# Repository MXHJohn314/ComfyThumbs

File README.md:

# ComfyThumbs

A column-staggered keyboard inspired by comfortable and efficient thumb use and keycap compatibility.

### The Default Keymap
<h5><b>Comfy Thumbs (v3)</b></h5>

[Check out the Gist on Keyboard Layout Editor](http://www.keyboard-layout-editor.com/#/gists/36e706f383088aca6e862086f8b5e326)

<p>

### High Keycap Compatibility

Comfy Thumbs has the highest keycap compatibility of any column-staggered board. Space and Backspace are the only keys that are not traditionally-sized. That means you won't need to buy/use different keycaps for `Right Shift`, `Left Shift`, `Enter`, `Tab`, `\ `, `Command`, `Ctrl`, `Alt`, `OS`, and `Application` keys. Just chose any Standard ANSI keycap set (99% of keycap sets), and you're good to go!. 

<p>

### Use your thumbs without hurting them

|Thumb Cluster Style|# of keys|Avg. reach from Home Position|
|---|---|---|
|ComfyThumbs|6|1u
|Manuform/Dactyl-Manuform|6|3.5u
|Maltron/Dacyl/Kenesis/Ergodox|6-8|4.5u

Unlike other large thumb cluster designs that waste valuable space by pushing the cluster away from resting thumb position or building the cluster on a convex plane, all thumb keys are within 1u radius of resting position. The thumbs naturally rest on either `Space` or `Backspace`, with `Shift`, `Ctrl`, `Alt` and `OS` nearby. There are two thumb rows; `Space`, `Backspace`, and both `Shift` keys have a higher profile on the upper thumb row to distinguish thumb location by feel.

### Comfy Thumbs = Comfy Pinkies
Your pinkies have been doing way more work than they should. That's why modifiers have moved to the thumb cluster. Adding to that, the index fingers have a new inner column for `Tab`, `\ `, `-`, `=`,  `[` and `]`.

Keyboard Maintainer: [MXHJohn314](https://mxhjohn314.github.io/)  

### Compiling the Firmware

See the [build environment setup](Todo) and the [make instructions](Todo) for more information. Brand new to ZMK? Start with our [Complete Newbs Guide](Todo).

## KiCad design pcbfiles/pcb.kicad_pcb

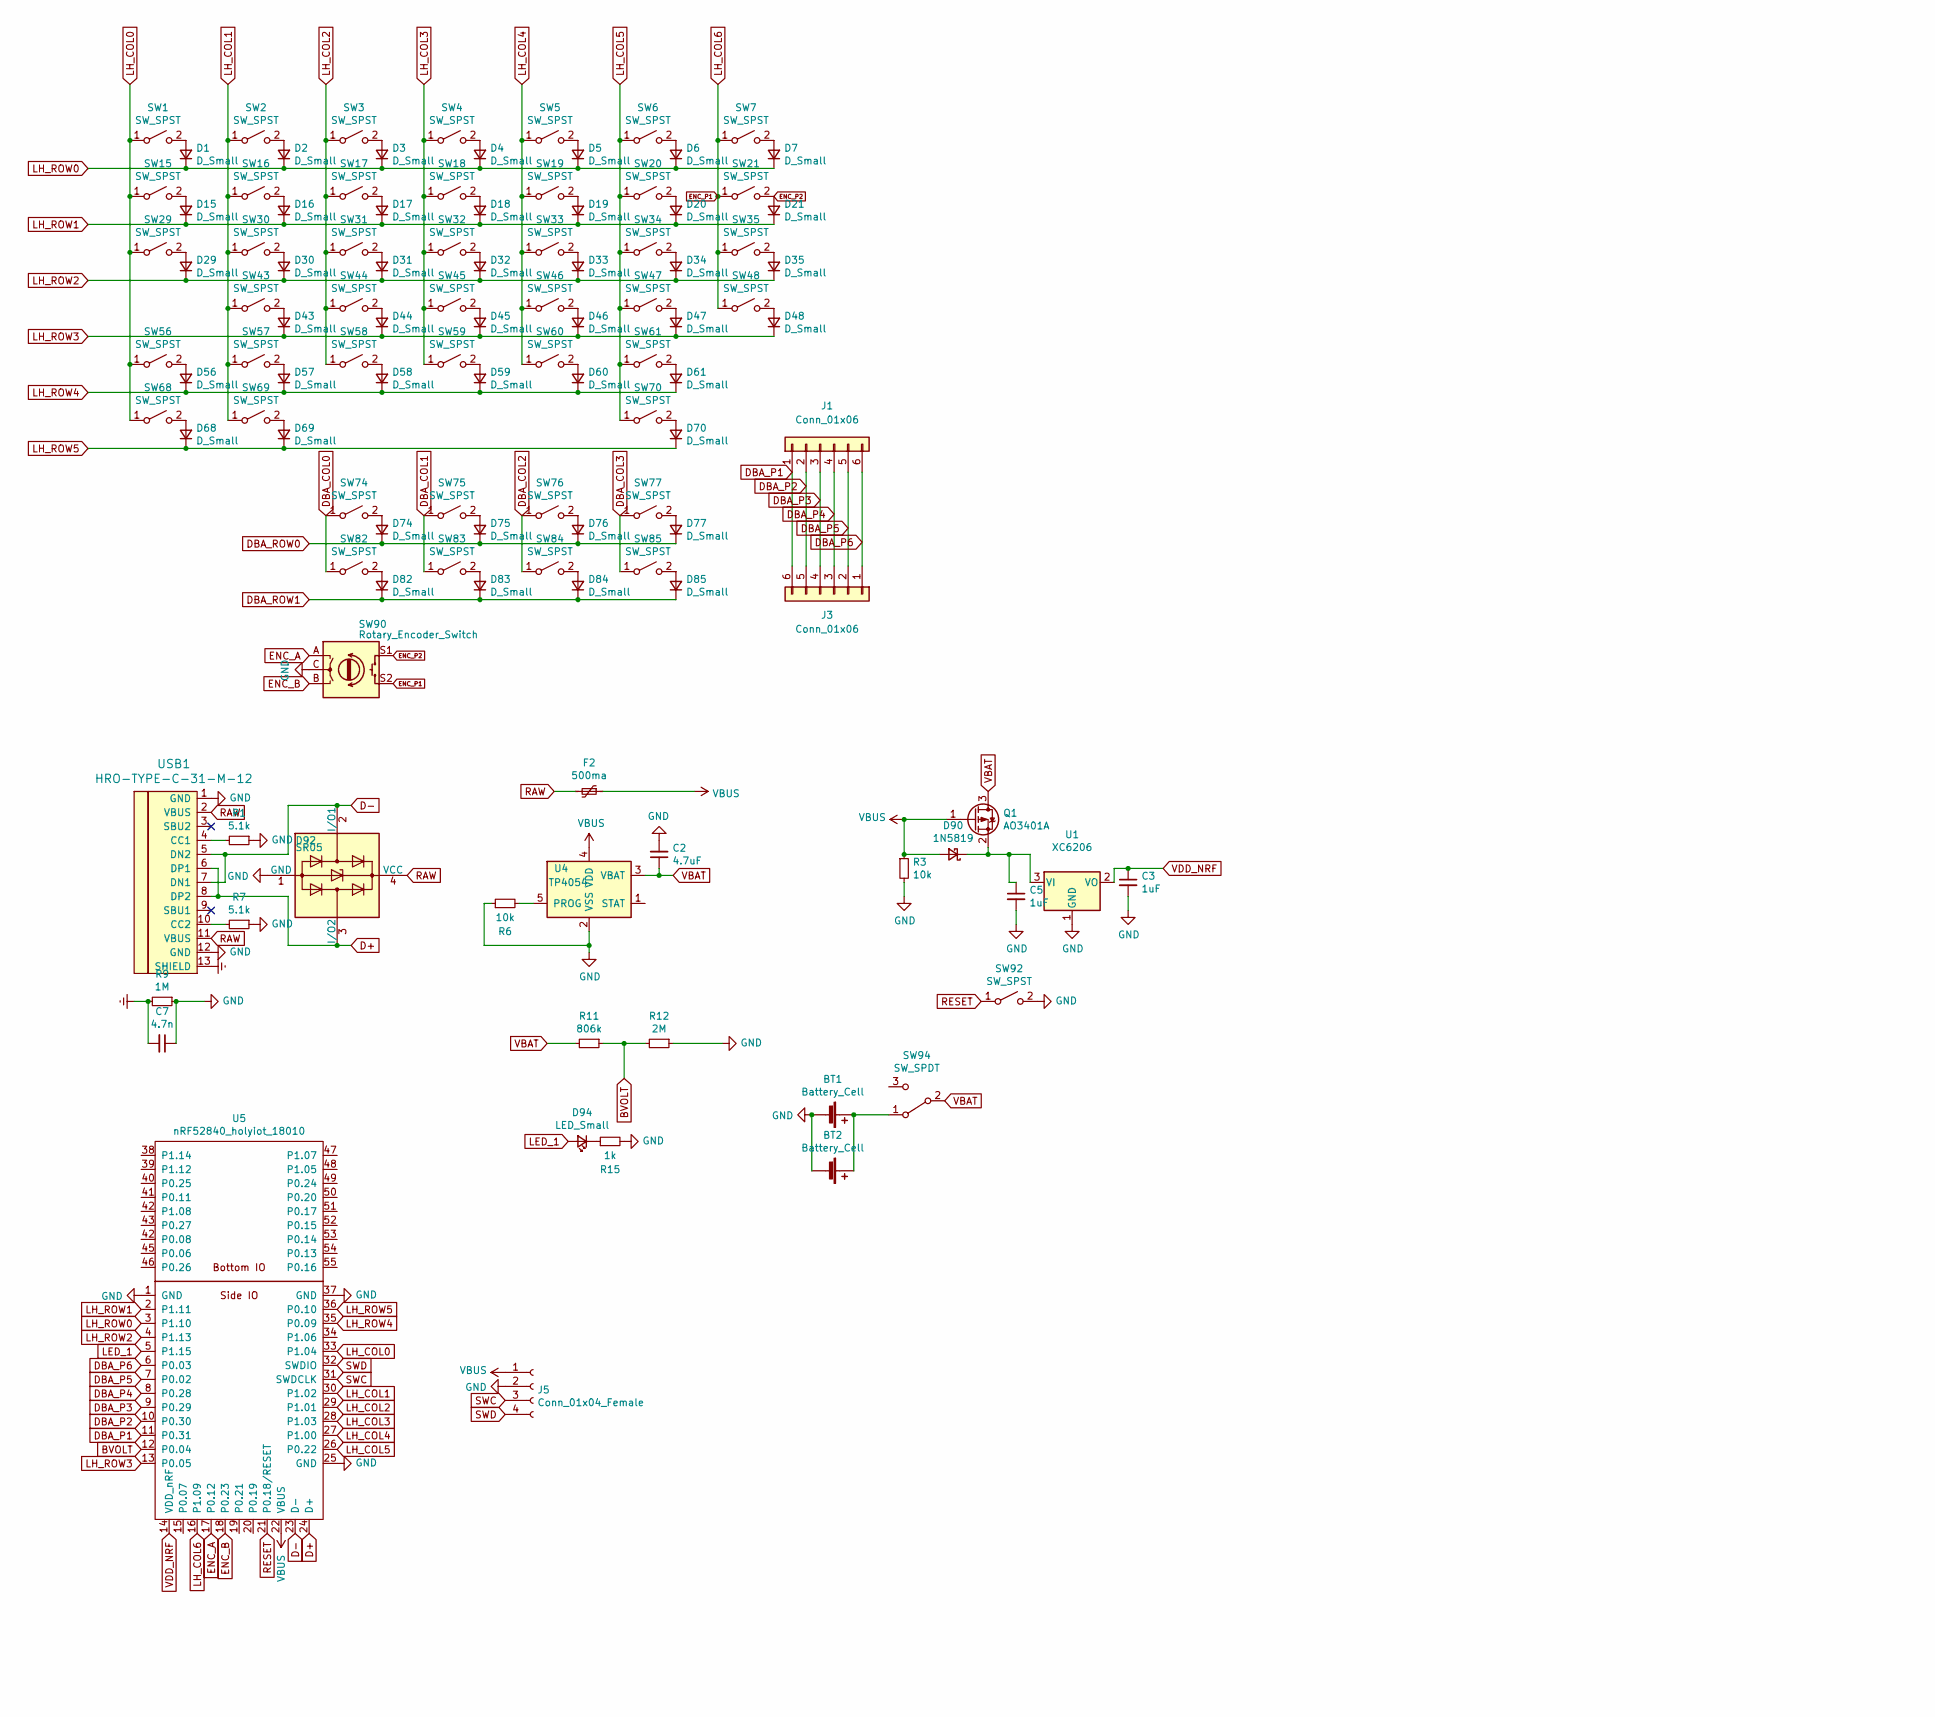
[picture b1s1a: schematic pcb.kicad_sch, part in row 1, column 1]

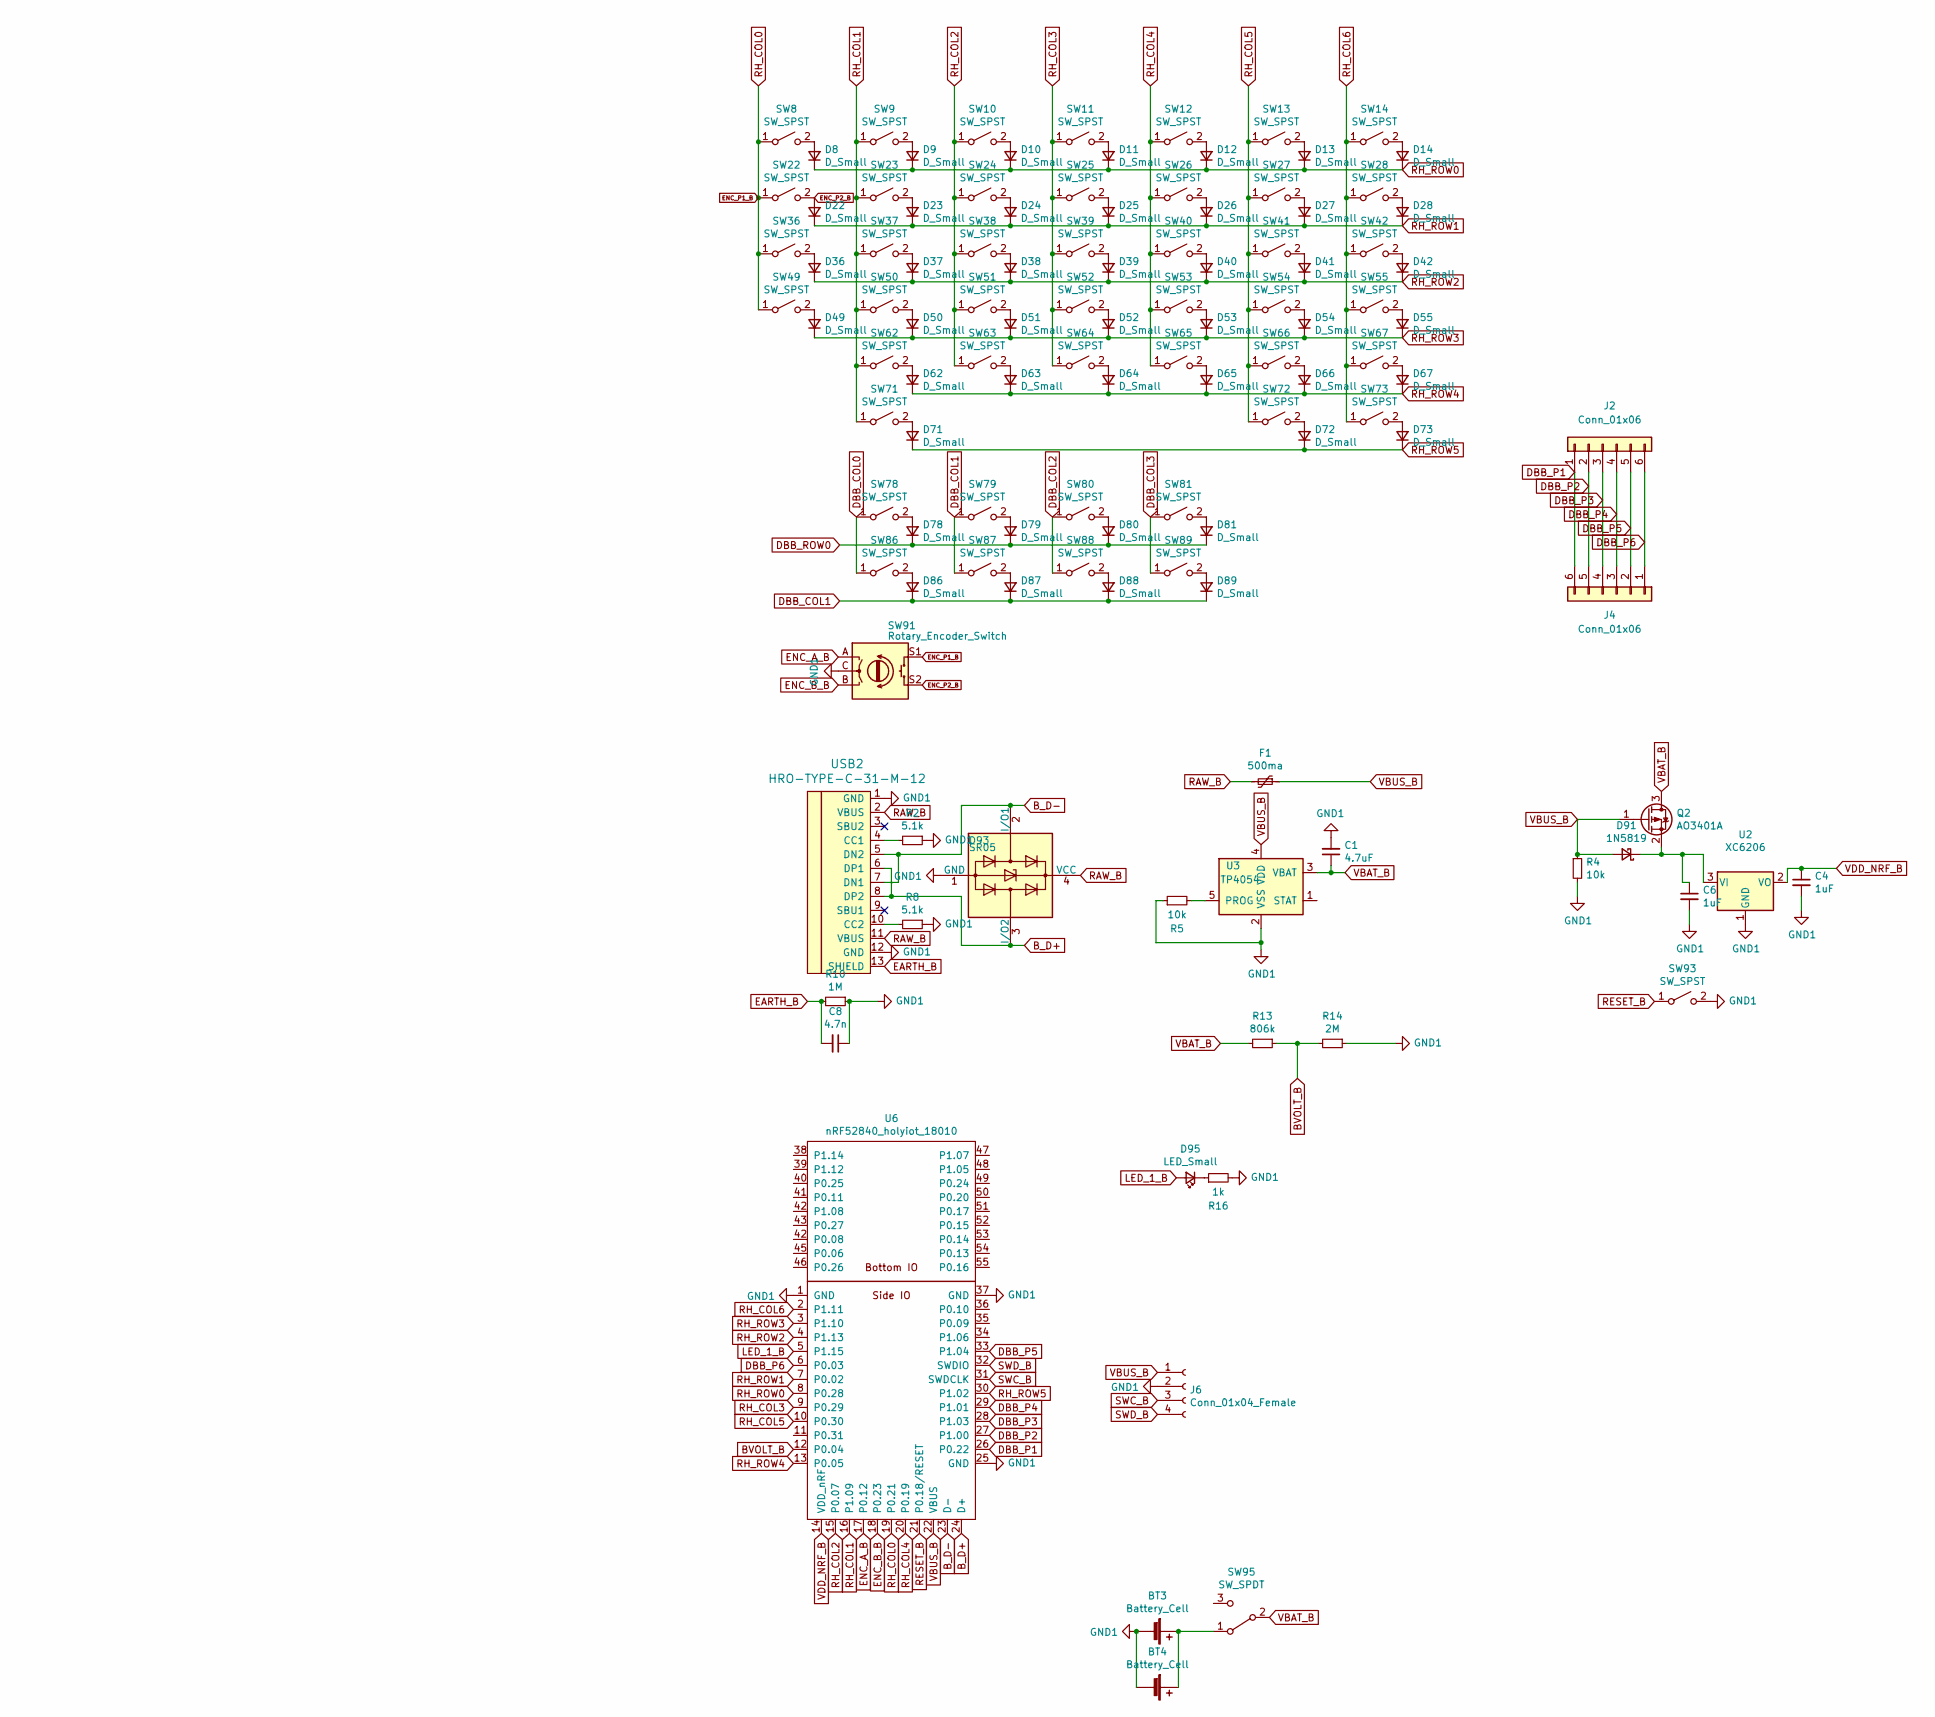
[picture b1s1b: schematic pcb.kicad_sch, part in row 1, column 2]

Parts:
BT1, BT3: Battery_Cell; JST_PH_S2B-PH-K_1x02_P2.00mm_Horizontal
BT2, BT4: Battery_Cell; battery-custom-connector
C1, C2: 4.7uF; C_0805_2012Metric
C3, C4, C5, C6: 1uF; C_0805_2012Metric
C7, C8: 4.7n; C_0805_2012Metric
D1, D2, D3, D4, D5, D6, D7, D8, D9, D10, D11, D12, D13, D14, D15, D16, D17, D18, D19, D20, D21, D22, D23, D24, D25, D26, D27, D28, D29, D30, D31, D32, D33, D34, D35, D36, D37, D38, D39, D40, D41, D42, D43, D44, D45, D46, D47, D48, D49, D50, D51, D52, D53, D54, D55, D56, D57, D58, D59, D60, D61, D62, D63, D64, D65, D66, D67, D68, D69, D70, D71, D72, D73, D74, D75, D76, D77, D78, D79, D80, D81, D82, D83, D84, D85, D86, D87, D88, D89: D_Small; D_SOD-123
D90, D91: 1N5819; D_SOD-123
D92, D93: SR05; SOT-143
D94, D95: LED_Small; D_0805_2012Metric
F1, F2: 500ma; Fuse_1206_3216Metric
J1, J2, J3, J4: Conn_01x06; JST_SH_SM06B-SRSS-TB_1x06-1MP_P1.00mm_Horizontal
J5, J6: Conn_01x04_Female; PinHeader_1x04_P2.54mm_Vertical
Q1, Q2: AO3401A; SOT-23
R1, R2, R7, R8: 5.1k; R_0805_2012Metric
R3, R4, R5, R6: 10k; R_0805_2012Metric
R9, R10: 1M; R_0805_2012Metric
R11, R13: 806k; R_0805_2012Metric
R12, R14: 2M; R_0805_2012Metric
R15, R16: 1k; R_0805_2012Metric
SW1, SW2, SW3, SW4, SW5, SW6, SW7, SW8, SW9, SW10, SW11, SW12, SW13, SW14, SW15, SW16, SW17, SW18, SW19, SW20, SW21, SW22, SW23, SW24, SW25, SW26, SW27, SW28, SW30, SW31, SW32, SW33, SW34, SW35, SW36, SW37, SW38, SW39, SW40, SW41, SW42, SW43, SW44, SW45, SW46, SW47, SW48, SW50, SW51, SW52, SW53, SW54, SW55, SW57, SW58, SW59, SW60, SW61, SW62, SW63, SW64, SW65, SW66, SW67, SW70, SW71, SW82, SW83, SW84, SW85, SW86, SW87, SW88, SW89: SW_SPST; MXOnly-1U-Hotswap
SW29, SW49: SW_SPST; MXOnly-1.5U-Hotswap
SW56: SW_SPST; MXOnly-1.75U-Hotswap
SW68, SW69, SW73, SW75, SW76, SW77, SW78, SW79, SW80: SW_SPST; MXOnly-1.25U-Hotswap
SW72: SW_SPST; MXOnly-2U-Hotswap
SW74: SW_SPST; MXOnly-2.75U-Hotswap
SW81: SW_SPST; MXOnly-2.25U-Hotswap
SW90, SW91: Rotary_Encoder_Switch; RotaryEncoder_Alps_EC11E-Switch_Vertical_H20mm
SW92, SW93: SW_SPST; SW_SPST_TL3342
SW94, SW95: SW_SPDT; SW_SPDT_PCM12
U1, U2: XC6206; SOT-23
U3, U4: TP4054; SOT-23-5
U5, U6: nRF52840_holyiot_18010; nRF52840_holyiot_18010_HS_simple
USB1, USB2: HRO-TYPE-C-31-M-12; HRO-TYPE-C-31-M-12-HandSoldering

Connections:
BVOLT: R11.1, R12.2, U5.12 (P0.04)
BVOLT_B: R13.1, R14.2, U6.12 (P0.04)
B_D+: D93.3 (I/O2), U6.24 (D+), USB2.6 (DP1), USB2.8 (DP2)
B_D-: D93.2 (I/O1), U6.23 (D-), USB2.5 (DN2), USB2.7 (DN1)
D+: D92.3 (I/O2), U5.24 (D+), USB1.6 (DP1), USB1.8 (DP2)
D-: D92.2 (I/O1), U5.23 (D-), USB1.5 (DN2), USB1.7 (DN1)
DBA_COL0: SW74.1 (A), SW82.1 (A)
DBA_COL1: SW75.1 (A), SW83.1 (A)
DBA_COL2: SW76.1 (A), SW84.1 (A)
DBA_COL3: SW77.1 (A), SW85.1 (A)
DBA_P1: J1.1, J3.6, U5.11 (P0.31)
DBA_P2: J1.2, J3.5, U5.10 (P0.30)
DBA_P3: J1.3, J3.4, U5.9 (P0.29)
DBA_P4: J1.4, J3.3, U5.8 (P0.28)
DBA_P5: J1.5, J3.2, U5.7 (P0.02)
DBA_P6: J1.6, J3.1, U5.6 (P0.03)
DBA_ROW0: D74.1 (K), D75.1 (K), D76.1 (K), D77.1 (K)
DBA_ROW1: D82.1 (K), D83.1 (K), D84.1 (K), D85.1 (K)
DBB_COL0: SW78.1 (A), SW86.1 (A)
DBB_COL1: D86.1 (K), D87.1 (K), D88.1 (K), D89.1 (K), SW79.1 (A), SW87.1 (A)
DBB_COL2: SW80.1 (A), SW88.1 (A)
DBB_COL3: SW81.1 (A), SW89.1 (A)
DBB_P1: J2.1, J4.6, U6.26 (P0.22)
DBB_P2: J2.2, J4.5, U6.27 (P1.00)
DBB_P3: J2.3, J4.4, U6.28 (P1.03)
DBB_P4: J2.4, J4.3, U6.29 (P1.01)
DBB_P5: J2.5, J4.2, U6.33 (P1.04)
DBB_P6: J2.6, J4.1, U6.6 (P0.03)
DBB_ROW0: D78.1 (K), D79.1 (K), D80.1 (K), D81.1 (K)
EARTH_B: C8.2, R10.2, USB2.13 (SHIELD)
ENC_A: SW90.A, U5.17 (P0.12)
ENC_A_B: SW91.A, U6.17 (P0.12)
ENC_B: SW90.B, U5.18 (P0.23)
ENC_B_B: SW91.B, U6.18 (P0.23)
ENC_P1: SW7.1 (A), SW21.1 (A), SW35.1 (A), SW48.1 (A), SW90.S2, U5.16 (P1.09)
ENC_P1_B: SW8.1 (A), SW22.1 (A), SW36.1 (A), SW49.1 (A), SW91.S1, U6.19 (P0.21)
ENC_P2: D21.2 (A), SW21.2 (B), SW90.S1
ENC_P2_B: D22.2 (A), SW22.2 (B), SW91.S2
Earth: C7.2, R9.2, USB1.13 (SHIELD)
GND: BT1.2 (-), BT2.2 (-), C2.2, C3.2, C5.2, C7.1, D92.1 (GND), J5.2, R1.1, R3.2, R6.1, R7.1, R9.1, R12.1, R15.2, SW90.C, SW92.2 (B), U1.1 (GND), U4.2 (VSS), U5.1 (GND), U5.25 (GND), U5.37 (GND), USB1.1 (GND), USB1.12 (GND)
GND1: BT3.2 (-), BT4.2 (-), C1.2, C4.2, C6.2, C8.1, D93.1 (GND), J6.2, R2.1, R4.2, R5.1, R8.1, R10.1, R14.1, R16.2, SW91.C, SW93.2 (B), U2.1 (GND), U3.2 (VSS), U6.1 (GND), U6.25 (GND), U6.37 (GND), USB2.1 (GND), USB2.12 (GND)
LED_1: D94.2 (A), U5.5 (P1.15)
LED_1_B: D95.2 (A), U6.5 (P1.15)
LH_COL0: SW1.1 (A), SW15.1 (A), SW29.1 (A), SW56.1 (A), SW68.1 (A), U5.33 (P1.04)
LH_COL1: SW2.1 (A), SW16.1 (A), SW30.1 (A), SW43.1 (A), SW57.1 (A), SW69.1 (A), U5.30 (P1.02)
LH_COL2: SW3.1 (A), SW17.1 (A), SW31.1 (A), SW44.1 (A), SW58.1 (A), U5.29 (P1.01)
LH_COL3: SW4.1 (A), SW18.1 (A), SW32.1 (A), SW45.1 (A), SW59.1 (A), U5.28 (P1.03)
LH_COL4: SW5.1 (A), SW19.1 (A), SW33.1 (A), SW46.1 (A), SW60.1 (A), U5.27 (P1.00)
LH_COL5: SW6.1 (A), SW20.1 (A), SW34.1 (A), SW47.1 (A), SW61.1 (A), SW70.1 (A), U5.26 (P0.22)
LH_ROW0: D1.1 (K), D2.1 (K), D3.1 (K), D4.1 (K), D5.1 (K), D6.1 (K), D7.1 (K), U5.3 (P1.10)
LH_ROW1: D15.1 (K), D16.1 (K), D17.1 (K), D18.1 (K), D19.1 (K), D20.1 (K), D21.1 (K), U5.2 (P1.11)
LH_ROW2: D29.1 (K), D30.1 (K), D31.1 (K), D32.1 (K), D33.1 (K), D34.1 (K), D35.1 (K), U5.4 (P1.13)
LH_ROW3: D43.1 (K), D44.1 (K), D45.1 (K), D46.1 (K), D47.1 (K), D48.1 (K), U5.13 (P0.05)
LH_ROW4: D56.1 (K), D57.1 (K), D58.1 (K), D59.1 (K), D60.1 (K), D61.1 (K), U5.35 (P0.09)
LH_ROW5: D68.1 (K), D69.1 (K), D70.1 (K), U5.36 (P0.10)
unnamed: BT1.1 (+), BT2.1 (+), SW94.1 (A)
unnamed: BT3.1 (+), BT4.1 (+), SW95.1 (A)
unnamed: C5.1, D90.1 (K), Q1.2 (S), U1.3 (VI)
unnamed: C6.1, D91.1 (K), Q2.2 (S), U2.3 (VI)
unnamed: D1.2 (A), SW1.2 (B)
unnamed: D2.2 (A), SW2.2 (B)
unnamed: D3.2 (A), SW3.2 (B)
unnamed: D4.2 (A), SW4.2 (B)
unnamed: D5.2 (A), SW5.2 (B)
unnamed: D6.2 (A), SW6.2 (B)
unnamed: D7.2 (A), SW7.2 (B)
unnamed: D8.2 (A), SW8.2 (B)
unnamed: D9.2 (A), SW9.2 (B)
unnamed: D10.2 (A), SW10.2 (B)
unnamed: D11.2 (A), SW11.2 (B)
unnamed: D12.2 (A), SW12.2 (B)
unnamed: D13.2 (A), SW13.2 (B)
unnamed: D14.2 (A), SW14.2 (B)
unnamed: D15.2 (A), SW15.2 (B)
unnamed: D16.2 (A), SW16.2 (B)
unnamed: D17.2 (A), SW17.2 (B)
unnamed: D18.2 (A), SW18.2 (B)
unnamed: D19.2 (A), SW19.2 (B)
unnamed: D20.2 (A), SW20.2 (B)
unnamed: D23.2 (A), SW23.2 (B)
unnamed: D24.2 (A), SW24.2 (B)
unnamed: D25.2 (A), SW25.2 (B)
unnamed: D26.2 (A), SW26.2 (B)
unnamed: D27.2 (A), SW27.2 (B)
unnamed: D28.2 (A), SW28.2 (B)
unnamed: D29.2 (A), SW29.2 (B)
unnamed: D30.2 (A), SW30.2 (B)
unnamed: D31.2 (A), SW31.2 (B)
unnamed: D32.2 (A), SW32.2 (B)
unnamed: D33.2 (A), SW33.2 (B)
unnamed: D34.2 (A), SW34.2 (B)
unnamed: D35.2 (A), SW35.2 (B)
unnamed: D36.2 (A), SW36.2 (B)
unnamed: D37.2 (A), SW37.2 (B)
unnamed: D38.2 (A), SW38.2 (B)
unnamed: D39.2 (A), SW39.2 (B)
unnamed: D40.2 (A), SW40.2 (B)
unnamed: D41.2 (A), SW41.2 (B)
unnamed: D42.2 (A), SW42.2 (B)
unnamed: D43.2 (A), SW43.2 (B)
unnamed: D44.2 (A), SW44.2 (B)
unnamed: D45.2 (A), SW45.2 (B)
unnamed: D46.2 (A), SW46.2 (B)
unnamed: D47.2 (A), SW47.2 (B)
unnamed: D48.2 (A), SW48.2 (B)
unnamed: D49.2 (A), SW49.2 (B)
unnamed: D50.2 (A), SW50.2 (B)
unnamed: D51.2 (A), SW51.2 (B)
unnamed: D52.2 (A), SW52.2 (B)
unnamed: D53.2 (A), SW53.2 (B)
unnamed: D54.2 (A), SW54.2 (B)
unnamed: D55.2 (A), SW55.2 (B)
unnamed: D56.2 (A), SW56.2 (B)
unnamed: D57.2 (A), SW57.2 (B)
unnamed: D58.2 (A), SW58.2 (B)
unnamed: D59.2 (A), SW59.2 (B)
unnamed: D60.2 (A), SW60.2 (B)
unnamed: D61.2 (A), SW61.2 (B)
unnamed: D62.2 (A), SW62.2 (B)
unnamed: D63.2 (A), SW63.2 (B)
unnamed: D64.2 (A), SW64.2 (B)
unnamed: D65.2 (A), SW65.2 (B)
unnamed: D66.2 (A), SW66.2 (B)
unnamed: D67.2 (A), SW67.2 (B)
unnamed: D68.2 (A), SW68.2 (B)
unnamed: D69.2 (A), SW69.2 (B)
unnamed: D70.2 (A), SW70.2 (B)
unnamed: D71.2 (A), SW71.2 (B)
unnamed: D72.2 (A), SW72.2 (B)
unnamed: D73.2 (A), SW73.2 (B)
unnamed: D74.2 (A), SW74.2 (B)
unnamed: D75.2 (A), SW75.2 (B)
unnamed: D76.2 (A), SW76.2 (B)
unnamed: D77.2 (A), SW77.2 (B)
unnamed: D78.2 (A), SW78.2 (B)
unnamed: D79.2 (A), SW79.2 (B)
unnamed: D80.2 (A), SW80.2 (B)
unnamed: D81.2 (A), SW81.2 (B)
unnamed: D82.2 (A), SW82.2 (B)
unnamed: D83.2 (A), SW83.2 (B)
unnamed: D84.2 (A), SW84.2 (B)
unnamed: D85.2 (A), SW85.2 (B)
unnamed: D86.2 (A), SW86.2 (B)
unnamed: D87.2 (A), SW87.2 (B)
unnamed: D88.2 (A), SW88.2 (B)
unnamed: D89.2 (A), SW89.2 (B)
unnamed: D94.1 (K), R15.1
unnamed: D95.1 (K), R16.1
unnamed: R1.2, USB1.4 (CC1)
unnamed: R2.2, USB2.4 (CC1)
unnamed: R5.2, U3.5 (PROG)
unnamed: R6.2, U4.5 (PROG)
unnamed: R7.2, USB1.10 (CC2)
unnamed: R8.2, USB2.10 (CC2)
RAW: D92.4 (VCC), F2.2, USB1.2 (VBUS), USB1.11 (VBUS)
RAW_B: D93.4 (VCC), F1.2, USB2.2 (VBUS), USB2.11 (VBUS)
RESET: SW92.1 (A), U5.21 (P0.18/RESET)
RESET_B: SW93.1 (A), U6.21 (P0.18/RESET)
RH_COL1: SW9.1 (A), SW23.1 (A), SW37.1 (A), SW50.1 (A), SW62.1 (A), SW71.1 (A), U6.16 (P1.09)
RH_COL2: SW10.1 (A), SW24.1 (A), SW38.1 (A), SW51.1 (A), SW63.1 (A), U6.15 (P0.07)
RH_COL3: SW11.1 (A), SW25.1 (A), SW39.1 (A), SW52.1 (A), SW64.1 (A), U6.9 (P0.29)
RH_COL4: SW12.1 (A), SW26.1 (A), SW40.1 (A), SW53.1 (A), SW65.1 (A), U6.20 (P0.19)
RH_COL5: SW13.1 (A), SW27.1 (A), SW41.1 (A), SW54.1 (A), SW66.1 (A), SW72.1 (A), U6.10 (P0.30)
RH_COL6: SW14.1 (A), SW28.1 (A), SW42.1 (A), SW55.1 (A), SW67.1 (A), SW73.1 (A), U6.2 (P1.11)
RH_ROW0: D8.1 (K), D9.1 (K), D10.1 (K), D11.1 (K), D12.1 (K), D13.1 (K), D14.1 (K), U6.8 (P0.28)
RH_ROW1: D22.1 (K), D23.1 (K), D24.1 (K), D25.1 (K), D26.1 (K), D27.1 (K), D28.1 (K), U6.7 (P0.02)
RH_ROW2: D36.1 (K), D37.1 (K), D38.1 (K), D39.1 (K), D40.1 (K), D41.1 (K), D42.1 (K), U6.4 (P1.13)
RH_ROW3: D49.1 (K), D50.1 (K), D51.1 (K), D52.1 (K), D53.1 (K), D54.1 (K), D55.1 (K), U6.3 (P1.10)
RH_ROW4: D62.1 (K), D63.1 (K), D64.1 (K), D65.1 (K), D66.1 (K), D67.1 (K), U6.13 (P0.05)
RH_ROW5: D71.1 (K), D72.1 (K), D73.1 (K), U6.30 (P1.02)
SWC: J5.3, U5.31 (SWDCLK)
SWC_B: J6.3, U6.31 (SWDCLK)
SWD: J5.4, U5.32 (SWDIO)
SWD_B: J6.4, U6.32 (SWDIO)
VBAT: C2.1, Q1.3 (D), R11.2, SW94.2 (B), U4.3 (VBAT)
VBAT_B: C1.1, Q2.3 (D), R13.2, SW95.2 (B), U3.3 (VBAT)
VBUS: D90.2 (A), F2.1, J5.1, Q1.1 (G), R3.1, U4.4 (VDD), U5.22 (VBUS)
VBUS_B: D91.2 (A), F1.1, J6.1, Q2.1 (G), R4.1, U3.4 (VDD), U6.22 (VBUS)
VDD_NRF: C3.1, U1.2 (VO), U5.14 (VDD_nRF)
VDD_NRF_B: C4.1, U2.2 (VO), U6.14 (VDD_nRF)

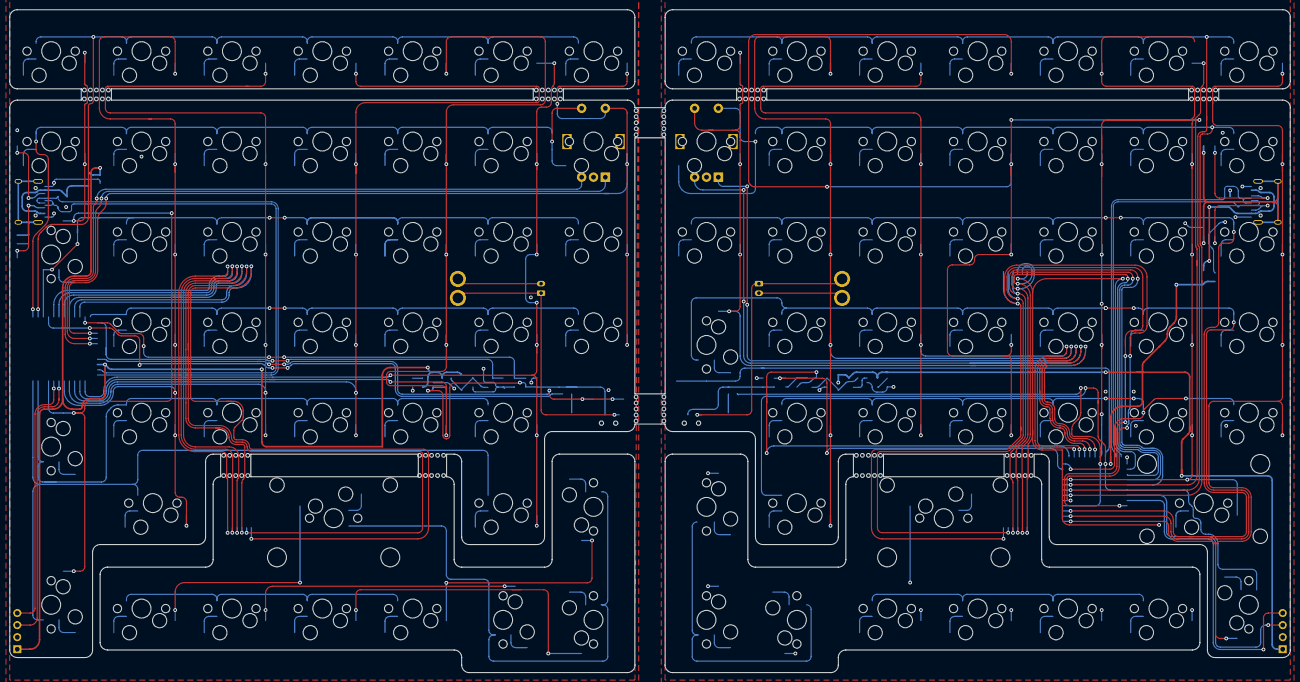
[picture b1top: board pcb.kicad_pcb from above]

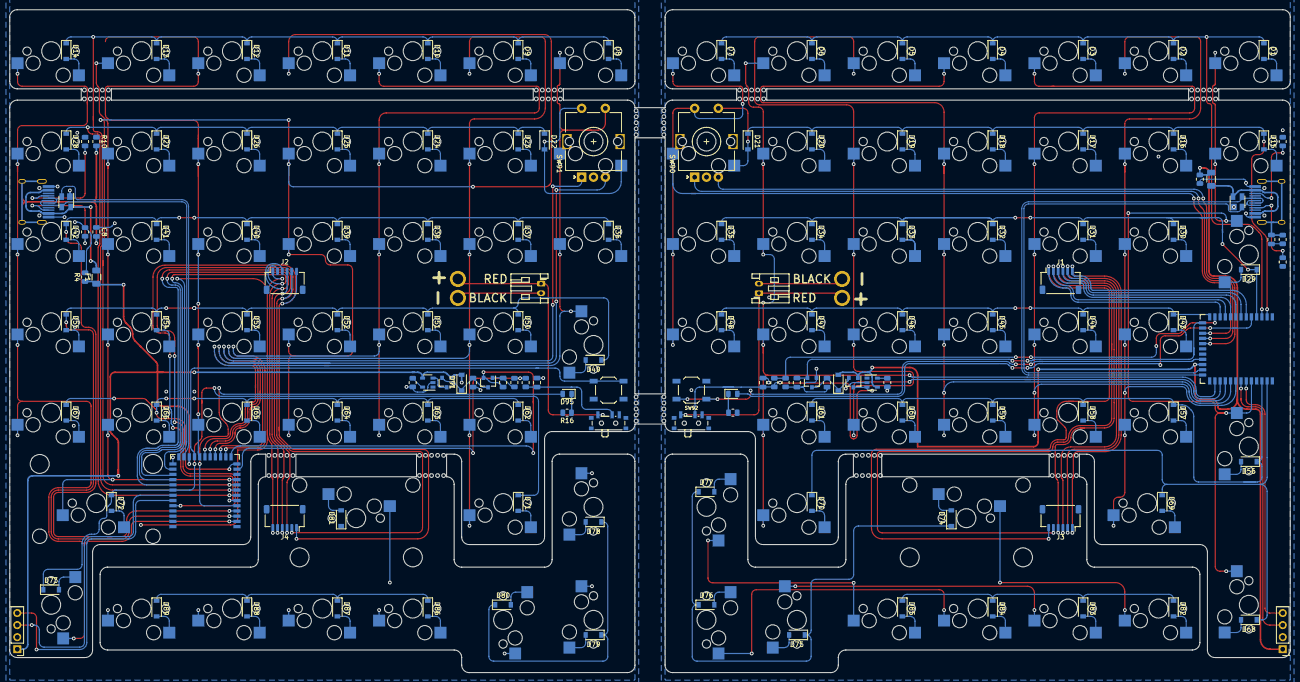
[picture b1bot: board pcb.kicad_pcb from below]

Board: 2 copper layers, 269.9 x 139.7 mm, 236 parts (145 on the bottom side), 180 nets.

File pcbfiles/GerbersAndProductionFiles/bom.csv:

Comment,Designator,Footprint,LCSC number,,
Battery_Cell,"BT1,BT3",battery-custom-connector,C173752,,
4.7n,"C7,C8",C_0805_2012Metric,C1744,,
1uF,"C6,C4,C3,C5",C_0805_2012Metric,C28323,,
SR05,"D93,D92",SOT-143,C384891,,
500ma,"F2,F1",Fuse_1206_3216Metric,C70076,,
AO3401A,"Q2,Q1",SOT-23,C306862,,
5.1k,"R1,R7,R2,R8",R_0805_2012Metric,C27834,,
10k,"R3,R5,R6,R4",R_0805_2012Metric,C17414,,
1k,"R15,R16",R_0805_2012Metric,C17513,,
806k,"R13,R11",R_0805_2012Metric,C63494,,
2M,"R14,R12",R_0805_2012Metric,C26112,,
SW_SPDT,"SW95,SW94",SW_SPDT_PCM12,C109335,,
TP4054,"U3,U4",SOT-23-5,C32574,,
XC6206,"U2,U1",SOT-23,C5446,,
HRO-TYPE-C-31-M-12,"USB1,USB2",HRO-TYPE-C-31-M-12-HandSoldering,C165948,,
SW_SPST,"SW93,SW92",SW_SPST_TL3342,C92584,,
4.7uF,"C1,C2",C_0805_2012Metric,C1779,,
LED_Small,"D94,D95",D_0805_2012Metric,C2296,,
1N5819,"D90,D91",D_SOD-123,C169540,,
1M,"R9,R10",R_0805_2012Metric,C17514,,
D_Small,"D12,D61,D53,D52,D31,D49,D81,D39,D11,D15,D5,D4,D88,D44,D74,D50,D82,D19,D79,D18,D54,D25,D1,D63,D42,D83,D75,D76,D35,D27,D59,D57,D10,D20,D7,D45,D84,D29,D69,D9,D37,D60,D78,D3,D22,D73,D46,D87,D24,D70,D47,D43,D36,D55,D66,D71,D23,D8,D68,D40,D56,D85,D41,D16,D28,D2,D67,D26,D51,D58,D34,D30,D32,D77,D38,D17,D33,D80,D64,D6,D89,D72,D65,D13,D14,D62,D86,D48,D21",D_SOD-123,C64898,,

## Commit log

2021-08-16 Create KiCad project, incomplete schematic
    KiCad project created, library submodules added, add gitignore, start schematic (split design, no matrix).
2021-08-16 Added README.md and layout picture
2021-08-18 continue schematic, test pcb idea
2021-08-21 PCB Layout, Diodes, Matrix
    Main body switches placed, some parts of matrix routed, PCB progress.
2021-08-22 Various commits
    I can't remember exactly what's changed since last time, but this is the most recent version!
2021-08-24 Various changes, finished placing switches
2021-08-25 Place components in new arrangement
2021-08-25 Further placement of parts
2021-08-28 USB wiring, etc...
2021-08-28 More wiring.
2021-08-29 Various changes.
2021-08-30 Final commit for the day.
2021-09-02 Step file, various kinds of progress.
2021-09-02 Added dxf files and case folder
2021-09-03 PCB progress
2021-09-04 Routing progress.
2021-09-04 More progress.
2021-09-04 more routing
2021-09-05 Save most recent routing.
2021-09-06 Finish all basic routing!
2021-09-06 Forgot to save the work I thought I had...
2021-09-07 Save work.
2021-09-07 These libraries made my KiCad crash.
2021-09-07 updated left and right plates using ai03 plate generator
2021-09-10 Almost there!
2021-09-10 Forgot to save before commit.
2021-09-12 finished commit sans production files
2021-09-12 Final! PCBs were ordered based off this commit.
2021-10-20 remove JST for thumb keys and move batt connector
2021-10-20 minor changes, production files
2021-10-20 updated step file
2022-01-12 Plate file updates, cleanup
2022-01-13 Restructure, add case files
2022-01-13 - Changed Fusion360 project name for case design from "TheComfyHands_BothFullyBuilt.f3z" to "project.f3z"
2022-01-22 Update README.md
    Fix typos.
2022-03-20 initial commit of KiCAD6 changes
2022-03-20 readme image
2022-03-20 update user profile link, broken...
2022-03-20 initial schematic work
2022-03-29 schematic changes
2022-03-30 Making really good progress on the left half.
2022-04-01 switch placement right side preliminary
2022-04-02 edgecuts and switches
2022-04-02 oops
2022-04-02 progress on placement, some routing, encoders
2022-04-06 part placements (incl USB), more work tomorrow
2022-04-06 battery connectors and much more
2022-04-08 pcb changes
2022-04-08 various routing
2022-04-08 All components are on the board!
2022-04-09 quite a bit of routing
2022-04-09 Incremental routing
2022-04-09 routing
2022-04-11 Today's minor progress
    I had a short break from responsibilities today, and made some progress. Discord wants to update and I'm data limited, so I can't message you right now, but I'm happy with my progress and appreciate 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
2022-04-12 Routing for the left half.
2022-04-15 practically done with the left half
2022-04-16 Routing.
2022-04-19 Significant work on Routing.
    right side!
2022-04-21 I'm so close I can feel it.
2022-04-23 DRC changes.
2022-04-23 Error correction.
2022-04-23 Error checking.
2022-04-23 Gerber Generation.
2022-04-23 Production outputs.
2022-04-23 Final production files.
2022-04-23 restructuring
